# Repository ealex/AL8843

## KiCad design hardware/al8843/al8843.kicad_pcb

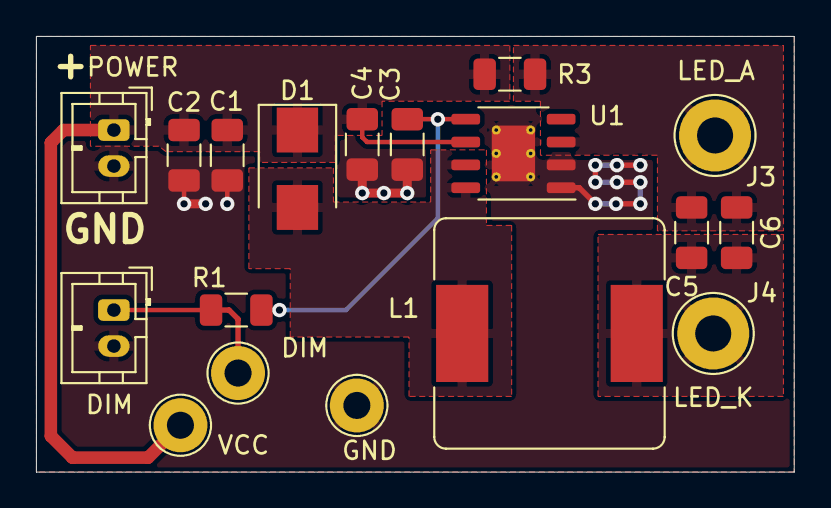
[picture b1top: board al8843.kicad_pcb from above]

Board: 2 copper layers, 42.1 x 24.2 mm, 18 parts (0 on the bottom side), 7 nets.

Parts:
C1, C2: UMK316AB7475KL-T; C_1206_3216Metric
C3: 1n; C_1206_3216Metric
C4: 100n; C_1206_3216Metric
C5, C6: CL21B105KBFNNNG; C_1206_3216Metric
D1: B360B-13-F; D_SMB
DIM: Conn_01x02; JST_PH_B2B-PH-K_1x02_P2.00mm_Vertical
DIM#2: CTRL_TP; TestPoint_Loop_D2.54mm_Drill1.5mm_Beaded
GND: GND_TP; TestPoint_Loop_D2.54mm_Drill1.5mm_Beaded
J3: LED_A; TestPoint_THTPad_D4.0mm_Drill2.0mm
J4: LED_K; TestPoint_THTPad_D4.0mm_Drill2.0mm
L1: SRR1260-330M; L_Bourns_SRR1260
POWER: Conn_01x02; JST_PH_B2B-PH-K_1x02_P2.00mm_Vertical
R1: DNP; R_1206_3216Metric
R3: 0.1; R_1206_3216Metric
U1: AL8843; HSOP-8-1EP_3.9x4.9mm_P1.27mm_EP2.41x3.1mm_ThermalVias
VCC: VCC_TP; TestPoint_Loop_D2.54mm_Drill1.5mm_Beaded

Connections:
/LED_A: C5.1, C6.1, J3.1, R3.1, U1.3
/LED_K: C5.2, C6.2, J4.1, L1.2
/VCC: C1.1, C2.1, C4.1, D1.1, POWER.1, R3.2, U1.6, VCC.1
GND: C1.2, C2.2, C3.2, C4.2, DIM.2, GND.1, POWER.2, U1.1, U1.2, U1.9
unnamed: C3.1, R1.1, U1.5
unnamed: D1.2, L1.1, U1.7, U1.8
unnamed: DIM.1, DIM#2.1, R1.2

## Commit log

2020-10-28 add documentation
2020-10-28 schematic and pcb, v1.0
2020-10-28 schematic as pdf
2020-10-28 clean-up
2023-11-11 update to latest kicad
2023-11-12 add values calculator
